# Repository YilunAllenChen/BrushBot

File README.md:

# BrushBot 2

This Repo serves the BrushBot 2.0 project from its hardware to its software.

## Project Structure
main.py: the program that ESP will execute once it boots up.\
ina219.py: Firmware for ina219 current sensor.\
vl6180Driver.py: Firmware for VL6180x sensor.\
logging.py: Supporting module for ina219 current sensor.\
DRV8836.py: Firmware for DRV8836 motor driver.

## Installation
Before the installation process begins, make sure your BrushBot is connected through FTDI to the computer.

You need to find the port connected to the BrushBot and replace "your_port" in the script below with that port. on Windows it should look like "COMx", mac "dev/xxxxx", linux "USB/ttyx".

Then run the script under the repo directory:

    python install.py your_port

The script provided by this repo will allow you to automatically install the dependencies of computer-brushbot interaction. Afterwards, it will attempt to installing the micropython firmware under the ./_MicroPython_bin directory to the BrushBot connected. This process involves erasing the flash and putting the bin file inside.

Once this is done, you can use the following script to automatically upload all your programs under ./Firmware directory to the robot. The your_port part is the same deal as the one with the install.py script.

    python Upload.py your_port

## INA219 Interface Example

```python
from ina219 import INA219
from machine import I2C

i2c = machine.I2C(-1,machine.Pin(22),machine.Pin(21)) #setup i2c
SHUNT_OHMS = 0.1 # Hardware setup - shunt resistance
ina = INA219(SHUNT_OHMS, i2c) # Create a sensor object
ina.configure() # Default configuration

# Usage
print("Bus Voltage: %.3f V" % ina.voltage())
print("Current: %.3f mA" % ina.current())
print("Power: %.3f mW" % ina.power())
```

## VL6180 Interface Example

```python
import machine
import sys
import utime
import vl6180_Driver

i2c = machine.I2C(-1,machine.Pin(22),machine.Pin(21)) #setup i2
sensor1 = vl6180_Driver.Sensor(i2c,41) # Create a sensor object

# Usage
print("Value read in address 41: " + str(sensor1.range()))
```

## DRV8836 Interface Example

```python
import machine #Required by machine.Pin
import DRV8836

A1 = machine.Pin(33) # Select the four pins used to control
A2 = machine.Pin(25) # the two motors
B1 = machine.Pin(26)
B2 = machine.Pin(27)
drv = DRV8836.DRV8836(A1, A2, B1, B2) # Create the motor driver object

# Usage
drv.testRun() # Test run function.
drv.setLeft(1000) # Set the motor output of left. -1023 ~ 1023.
drv.stop()
```

## TCP-IP
Note: In order for the Controller to work, the server side computer needs to allow TCP/IP inbound/outbound connections on port 23.

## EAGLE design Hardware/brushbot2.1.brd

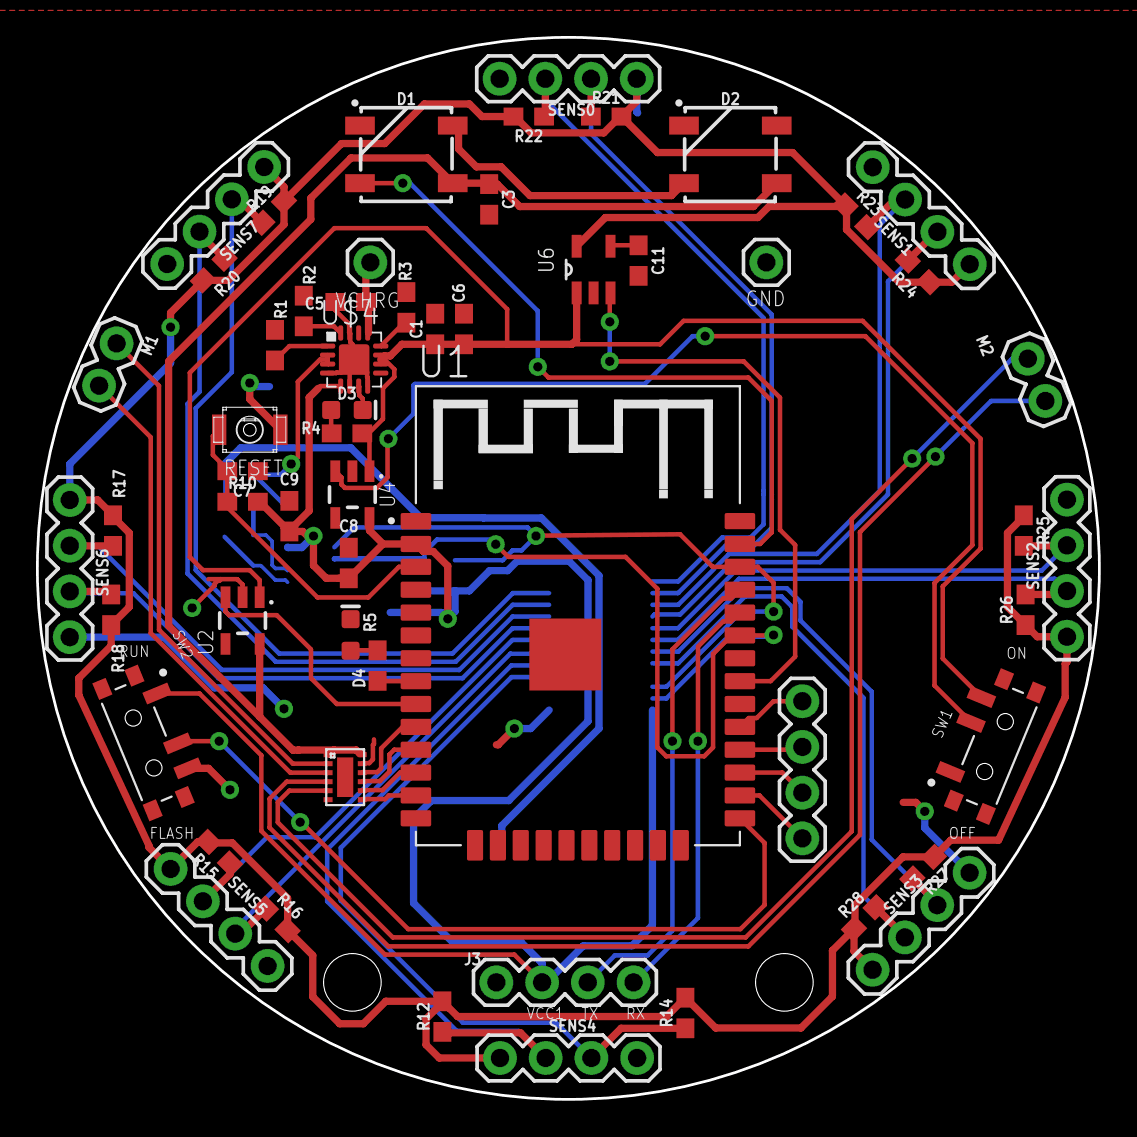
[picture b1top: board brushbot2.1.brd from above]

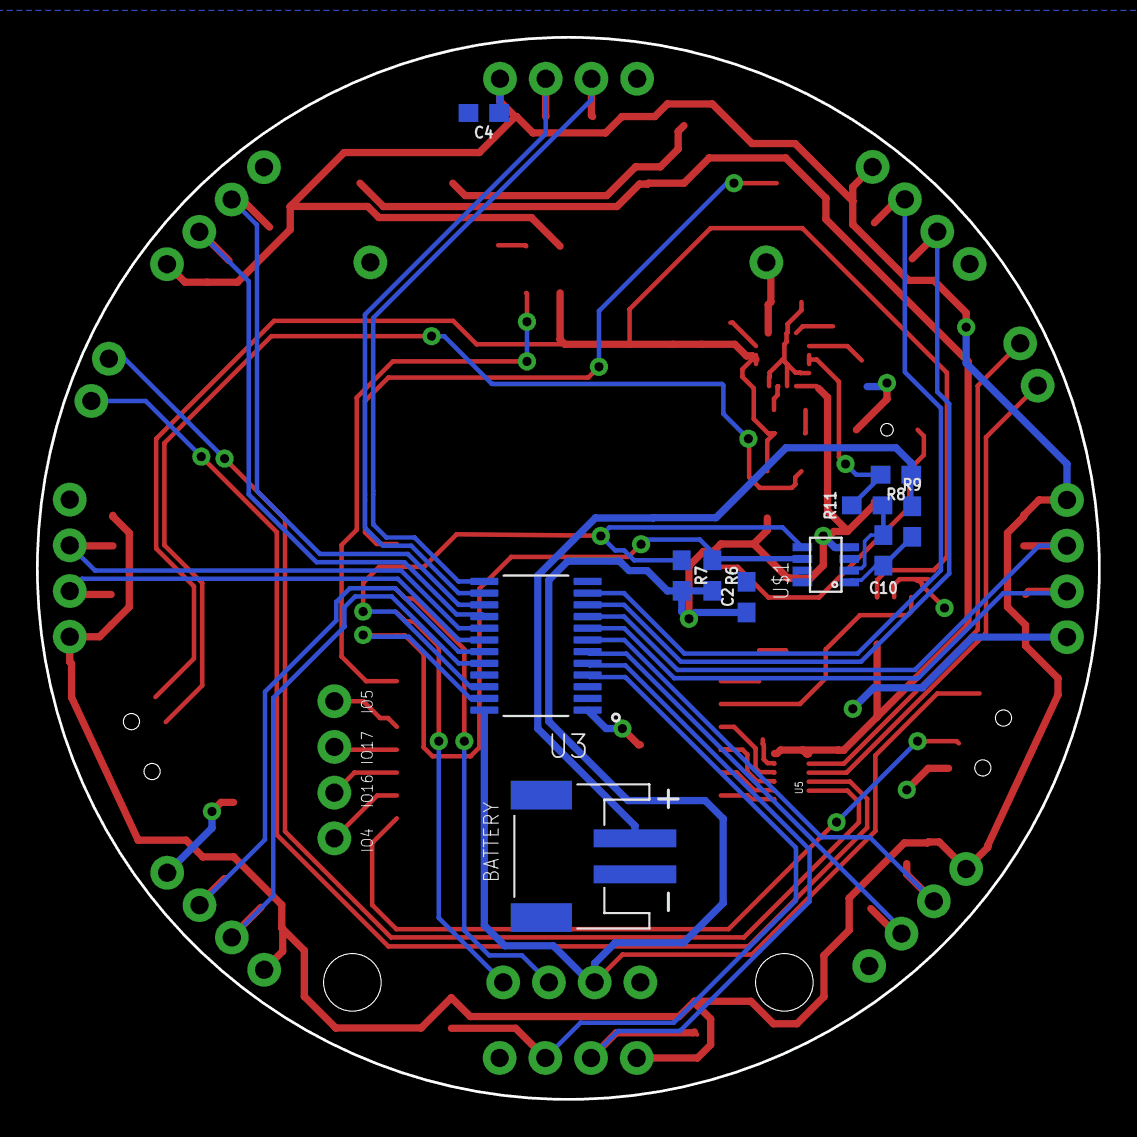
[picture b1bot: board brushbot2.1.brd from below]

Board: 2 copper layers, 59.0 x 59.0 mm, 69 parts (11 on the bottom side), 57 nets.

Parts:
C1, C2, C3, C5: 1.0uF; 0603
C4: 10uF; 0603
C6: 4.7uF; 0603
C7, C8, C9, C10: 0.1uF; 0603
C11: 10nF; 0603
CN1: JST-PH-2-SMT-RA
D1, D2: WS2812B
D3, D4: RED; LED-0603
FRAME2: FRAME-LEDGER; CREATIVE_COMMONS
J3, J12: 1X04
J4, J5: 1X01
M1, M2: 1X02
R1, R10: 10k; 0603
R2: 1.8k; 0603
R3, R4: 1k; 0603
R5: 47k; 0603
R6, R7, R12, R14, R15, R16, R17, R18, R19, R20, R21, R22, R23, R24, R25, R26, R27, R28: 4.7k; 0603
R8: 0.05; 0603
R9, R11: 10; 0603
RST_BUTTON: BUTTON_TACTILE_SLIM
SENS0, SENS1, SENS2, SENS3, SENS4, SENS5, SENS6, SENS7: 1X04
SW1, SW2: PCM12SMTR; SW_PCM12SMTR
U1: ESP-WROOM-32; MODULE_ESP-WROOM-32
U2, U4: 3.3V; SOT23-5
U3: TCA9548APWR; SOP65P640X120-24N
U5: DRV8836; 12WSON
U6: TPS79328DBVR; SOT95P280X145-5N
U$1: INA219; SOT-23-8
U$4: BQ24075; QFN16

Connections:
26: J12.1, U1.26
27: J12.2, U1.27
28: J12.3, U1.28
29: J12.4, U1.29
AIN1: U1.10, U5.10
AIN2: U1.11, U5.9
BIN1: U1.12, U5.8
BIN2: U1.13, U5.7
GND: C1.2, C2.2, C3.2, C4.2, C5.2, C6.2, C7.1, C8.1, C9.1, C11.2, CN1.2, D1.3, D2.3, D4.C, J3.1, J5.1, R1.1, R2.1, R3.2, RST_BUTTON.2, SENS0.4, SENS1.4, SENS2.4, SENS3.4, SENS4.4, SENS5.4, SENS6.4, SENS7.4, SW1.1, SW2.3, U1.1, U1.1.1, U1.15, U1.38, U2.2, U3.1, U3.2, U3.12, U3.21, U4.2, U5.6, U5.11, U6.2, U$1.3, U$1.7, U$1.8, U$4.4, U$4.6, U$4.8, U$4.15, U$4.TH
GPIO0: SW2.2, U1.25
LED1OUT: D1.2, D2.4
LEDS: D1.4, U1.37
M1+: M1.1, U5.2
M1-: M1.2, U5.3
M2+: M2.1, U5.4
M2-: M2.2, U5.5
MOTOR_EN: U1.9, U2.3
unnamed: R1.2, U$4.1
unnamed: SW1.2, U4.3
unnamed: R2.2, U$4.16
unnamed: R3.1, U$4.12
unnamed: C10.1, R9.2, U$1.1
unnamed: D3.C, U$4.7
unnamed: D3.A, R4.1
unnamed: R5.2, U1.8
unnamed: D4.A, R5.1
unnamed: C10.2, R11.2, U$1.2
unnamed: CN1.1, R8.1, R9.1
unnamed: C11.1, U6.4
RESET: C7.2, R10.1, RST_BUTTON.1, U1.3
SCL1: R7.1, U1.36, U3.22, U$1.5
SCL1_0: R21.1, SENS0.2, U3.14
SCL1_1: R24.2, SENS1.2, U3.16
SCL1_2: R26.2, SENS2.2, U3.18
SCL1_3: R28.2, SENS3.2, U3.20
SCL1_4: R12.1, SENS4.2, U3.5
SCL1_5: R15.1, SENS5.2, U3.7
SCL1_6: R17.1, SENS6.2, U3.9
SCL1_7: R19.1, SENS7.2, U3.11
SDA1: R6.1, U1.33, U3.23, U$1.6
SDA1_0: R22.1, SENS0.3, U3.13
SDA1_1: R23.2, SENS1.3, U3.15
SDA1_2: R25.2, SENS2.3, U3.17
SDA1_3: R27.2, SENS3.3, U3.19
SDA1_4: R14.1, SENS4.3, U3.4
SDA1_5: R16.1, SENS5.3, U3.6
SDA1_6: R18.1, SENS6.3, U3.8
SDA1_7: R20.1, SENS7.3, U3.10
SENS_EN: U1.31, U6.3
U0RX: J3.4, U1.34
U0TX: J3.3, U1.35
VBAT: R8.2, R11.1, U$4.2, U$4.3
VCC1: C2.1, C8.2, C9.2, J3.2, R6.2, R7.2, R10.2, SW2.1, U1.2, U3.24, U4.5, U$1.4, U$4.5
VCC2: C3.1, D1.1, D2.1, U2.5, U5.1, U5.12
VCC3: C4.1, R12.2, R14.2, R15.2, R16.2, R17.2, R18.2, R19.2, R20.2, R21.2, R22.2, R23.1, R24.1, R25.1, R26.1, R27.1, R28.1, SENS0.1, SENS1.1, SENS2.1, SENS3.1, SENS4.1, SENS5.1, SENS6.1, SENS7.1, U6.5
VCHRG: C5.1, J4.1, U$4.13
V_SUP: C1.1, C6.1, R4.2, SW1.3, U2.1, U4.1, U6.1, U$4.10, U$4.11

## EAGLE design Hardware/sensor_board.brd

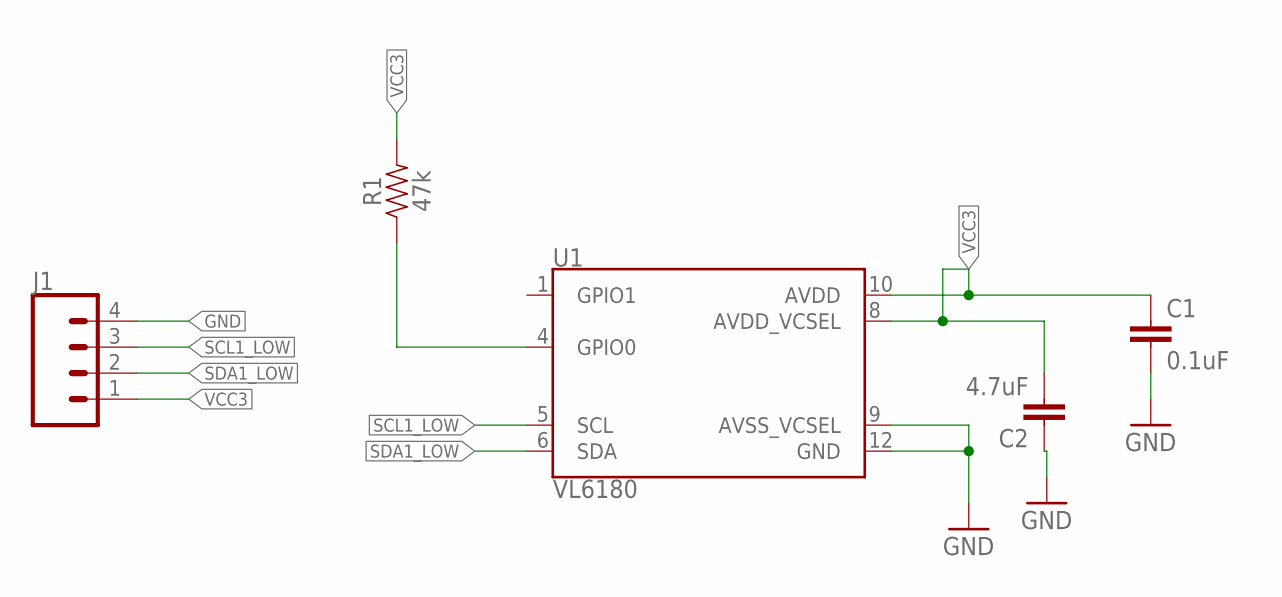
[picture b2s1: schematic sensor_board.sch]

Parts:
C1: 0.1uF; 0603
C2: 4.7uF; 0603
J1: CONN_04PTH; 1X04
R1: 47k; 0603
U1: VL6180

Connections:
GND: C1.2, C2.1, J1.4, U1.9 (AVSS_VCSEL), U1.12 (GND)
unnamed: R1.1, U1.4 (GPIO0)
SCL1_LOW: J1.3, U1.5 (SCL)
SDA1_LOW: J1.2, U1.6 (SDA)
VCC3: C1.1, C2.2, J1.1, R1.2, U1.8 (AVDD_VCSEL), U1.10 (AVDD)

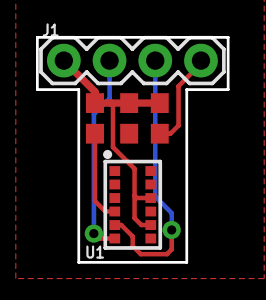
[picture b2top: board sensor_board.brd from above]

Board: 2 copper layers, 10.6 x 12.5 mm, 5 parts (0 on the bottom side), 5 nets.

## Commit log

2019-06-13 adding esp32 firmware bin file and a test python script
2019-06-14 Adding schematics; Fixed main.py
2019-06-14 added setup and upload script in batch
2019-06-20 main.py updated with i2c enabled. Added vl6180 driver. Updated schematics.
2019-06-20 Removed Early Convergence Time Check
2019-06-23 updated schematics
2019-07-02 final board design uploaded
2019-07-08 final PCB layout added
2019-07-08 organized the project. Adding a manual
2019-07-08 added readme
2019-07-08 readme updated.
2019-07-08 main.py updated
2019-07-16 changed auto-upload script to python file.
2019-07-16 updated readme, ina219 functions properly now
2019-07-16 fixed typo
2019-07-16 Updated Components
2019-07-17 vl6180x now come in list
2019-07-17 Renamed dirs
2019-07-23 new configureVL6180x, modified main, improved install and upload
2019-07-24 LED configured for custom BrushBot board
2019-07-24 neoPixels configured
2019-07-24 Better looking initialization messages
2019-07-29 BrushBot 2.1 board design completed
2019-07-30 new DRV8836 driver, cleaned up hardware files
2019-07-30 fixed a bug in VL6180 firmware
2019-07-30 improved readme
2019-08-01 test program updated
2019-08-05 updated install.py; tested Controller module; Tested and archived TCP/IP tester module;
2019-08-06 Improved explanation for main.py
2019-08-06 improved networking program; improved main.py
2019-08-06 stopped keyboard detection tempararily
2019-08-07 improved install.py and upload.py, improved Readme.md
2019-08-07 fixed typo in readme
2019-08-07 organized imports
2019-08-07 added more detailed explanation in readme.md
2019-09-27 updates, removed problematic ampy install

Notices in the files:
parts and their libraries:
SparkFun-IC-Power: Licensing: Creative Commons ShareAlike 4.0 International - https://creativecommons.org/licenses/by-sa/4.0
